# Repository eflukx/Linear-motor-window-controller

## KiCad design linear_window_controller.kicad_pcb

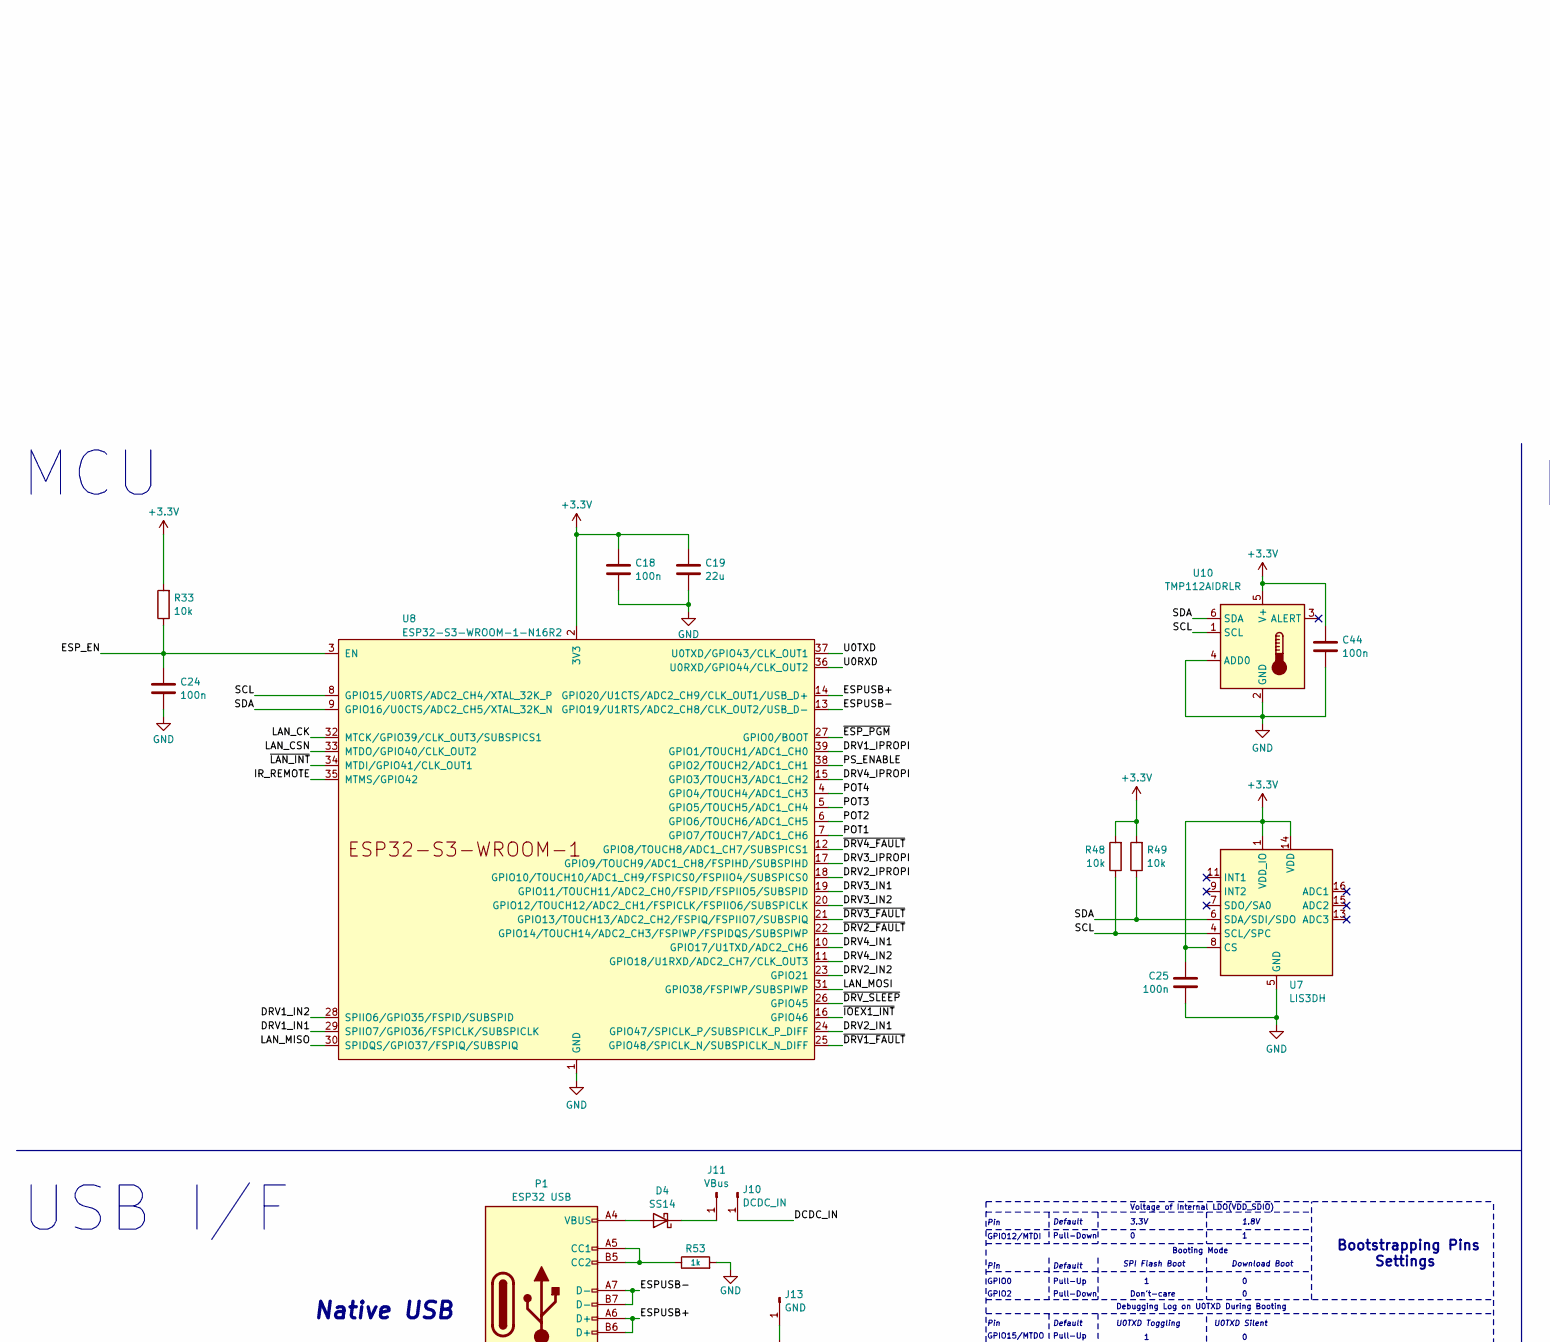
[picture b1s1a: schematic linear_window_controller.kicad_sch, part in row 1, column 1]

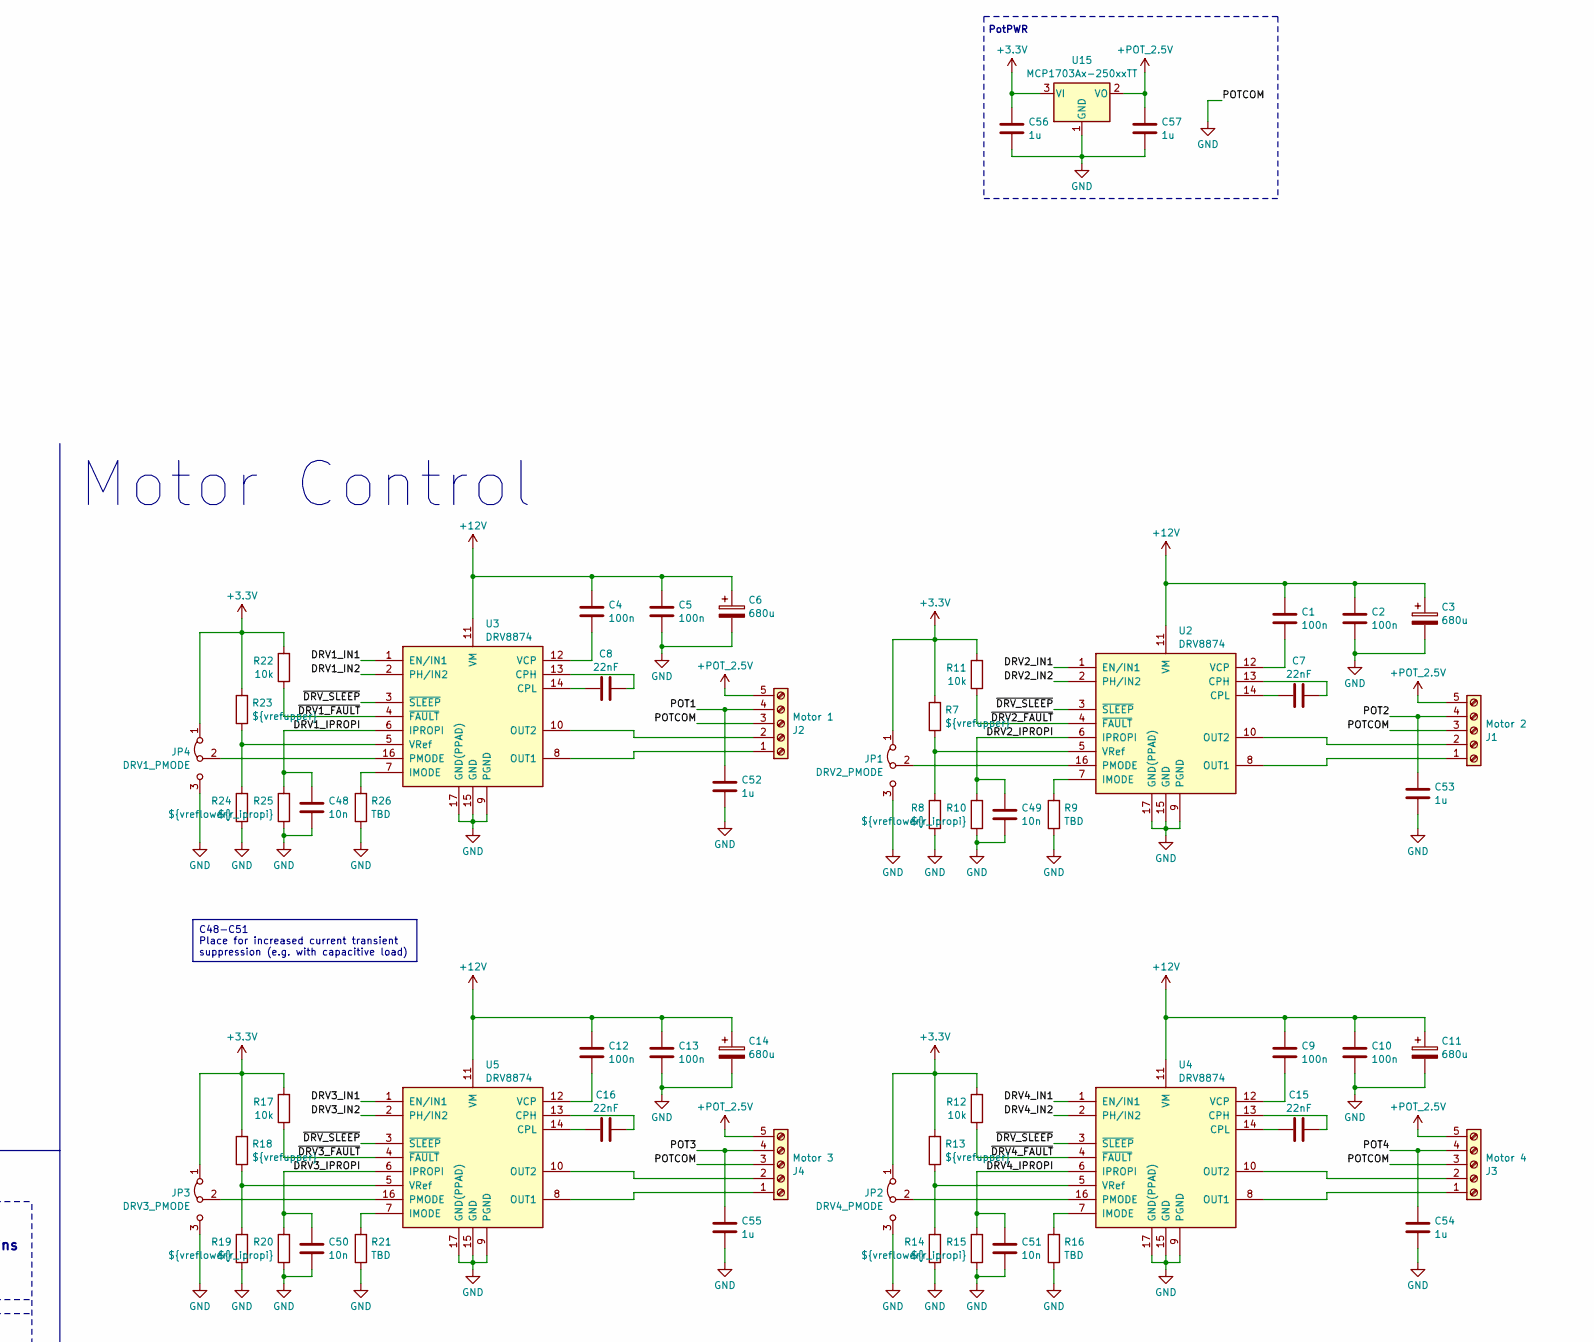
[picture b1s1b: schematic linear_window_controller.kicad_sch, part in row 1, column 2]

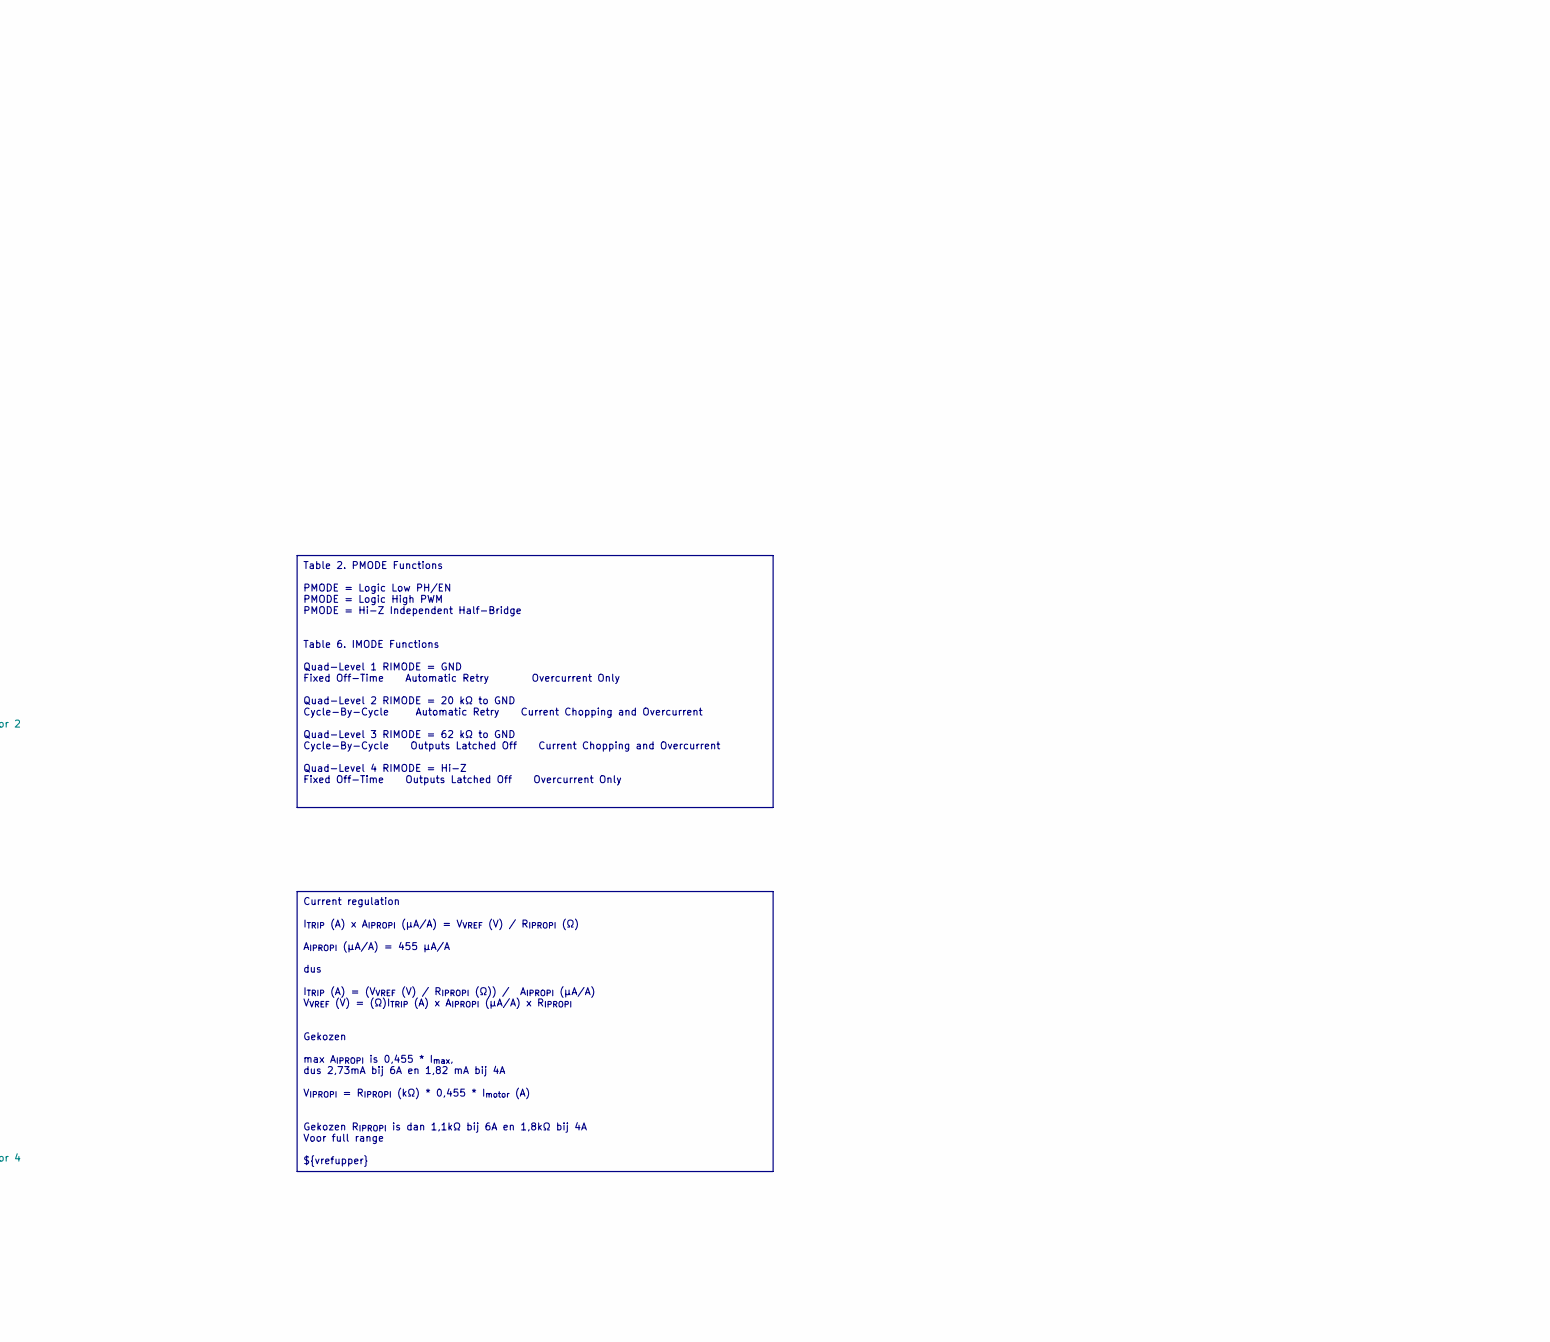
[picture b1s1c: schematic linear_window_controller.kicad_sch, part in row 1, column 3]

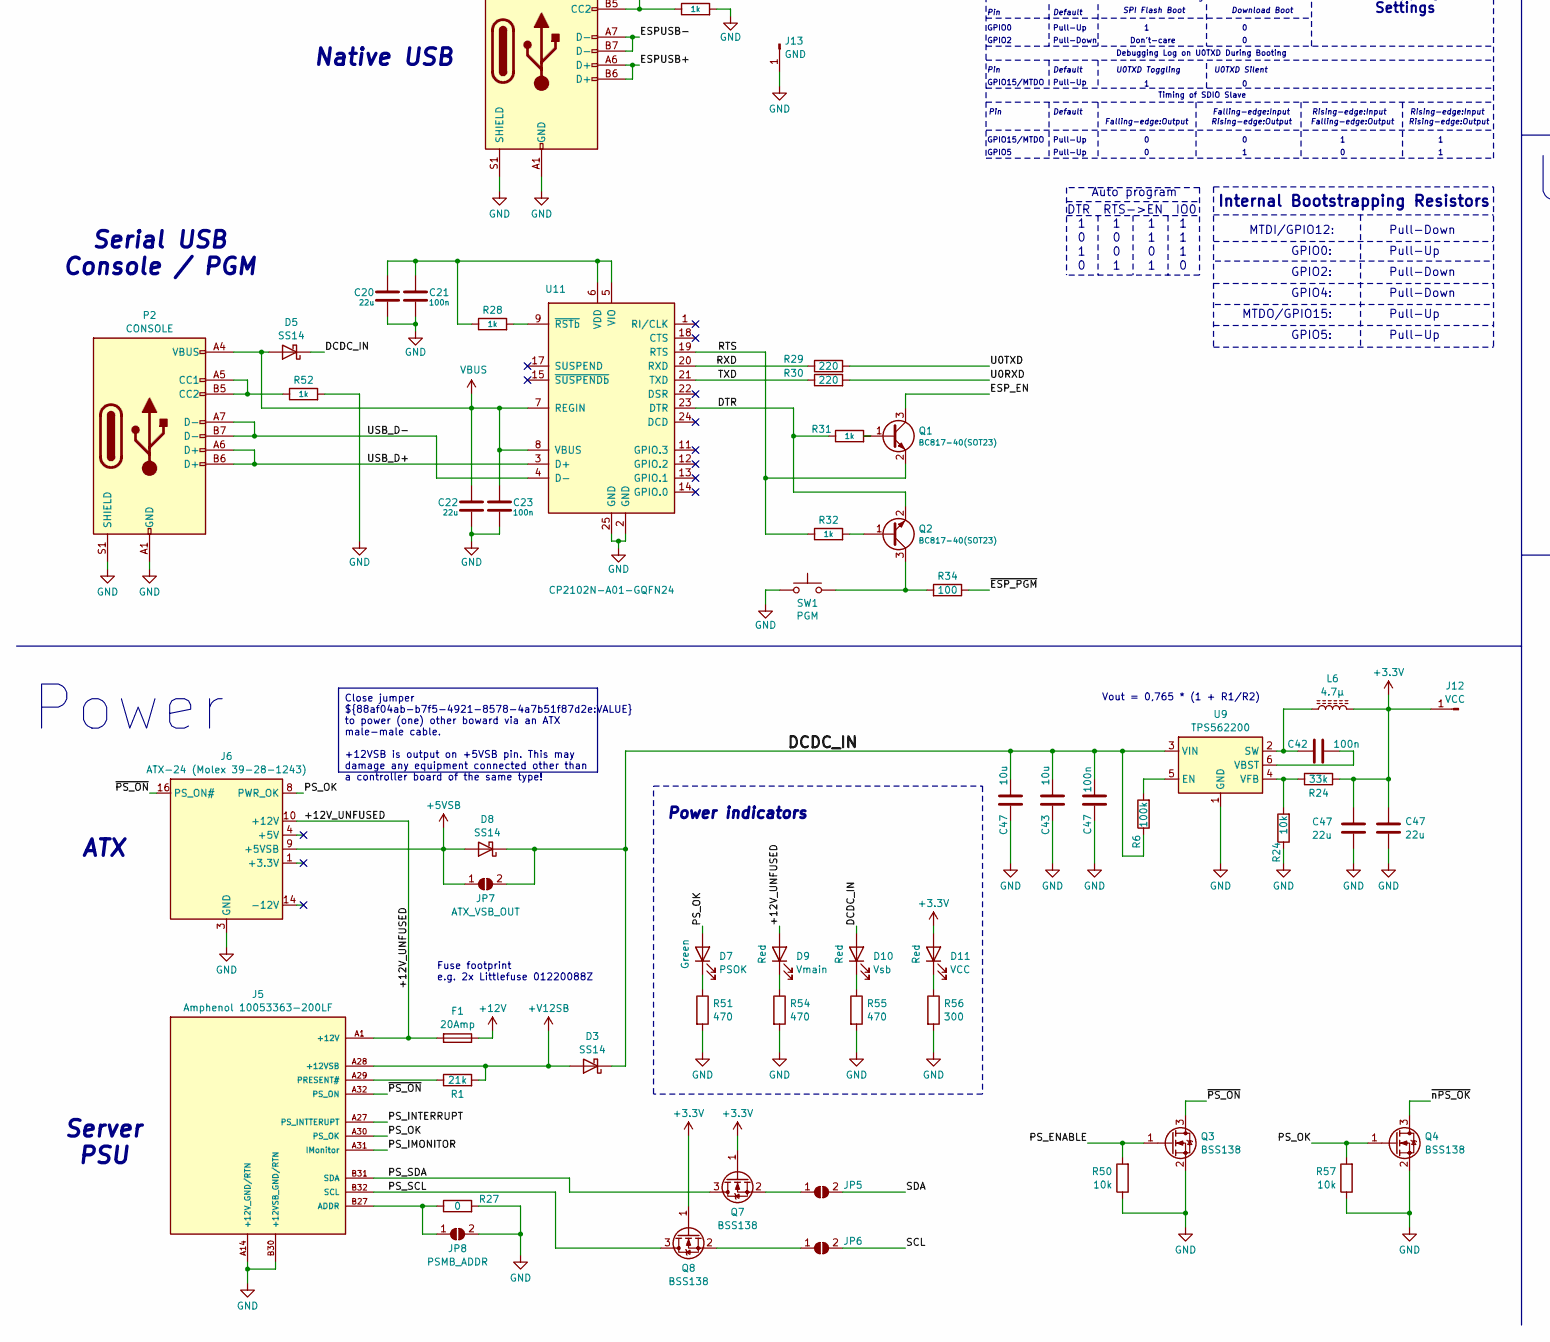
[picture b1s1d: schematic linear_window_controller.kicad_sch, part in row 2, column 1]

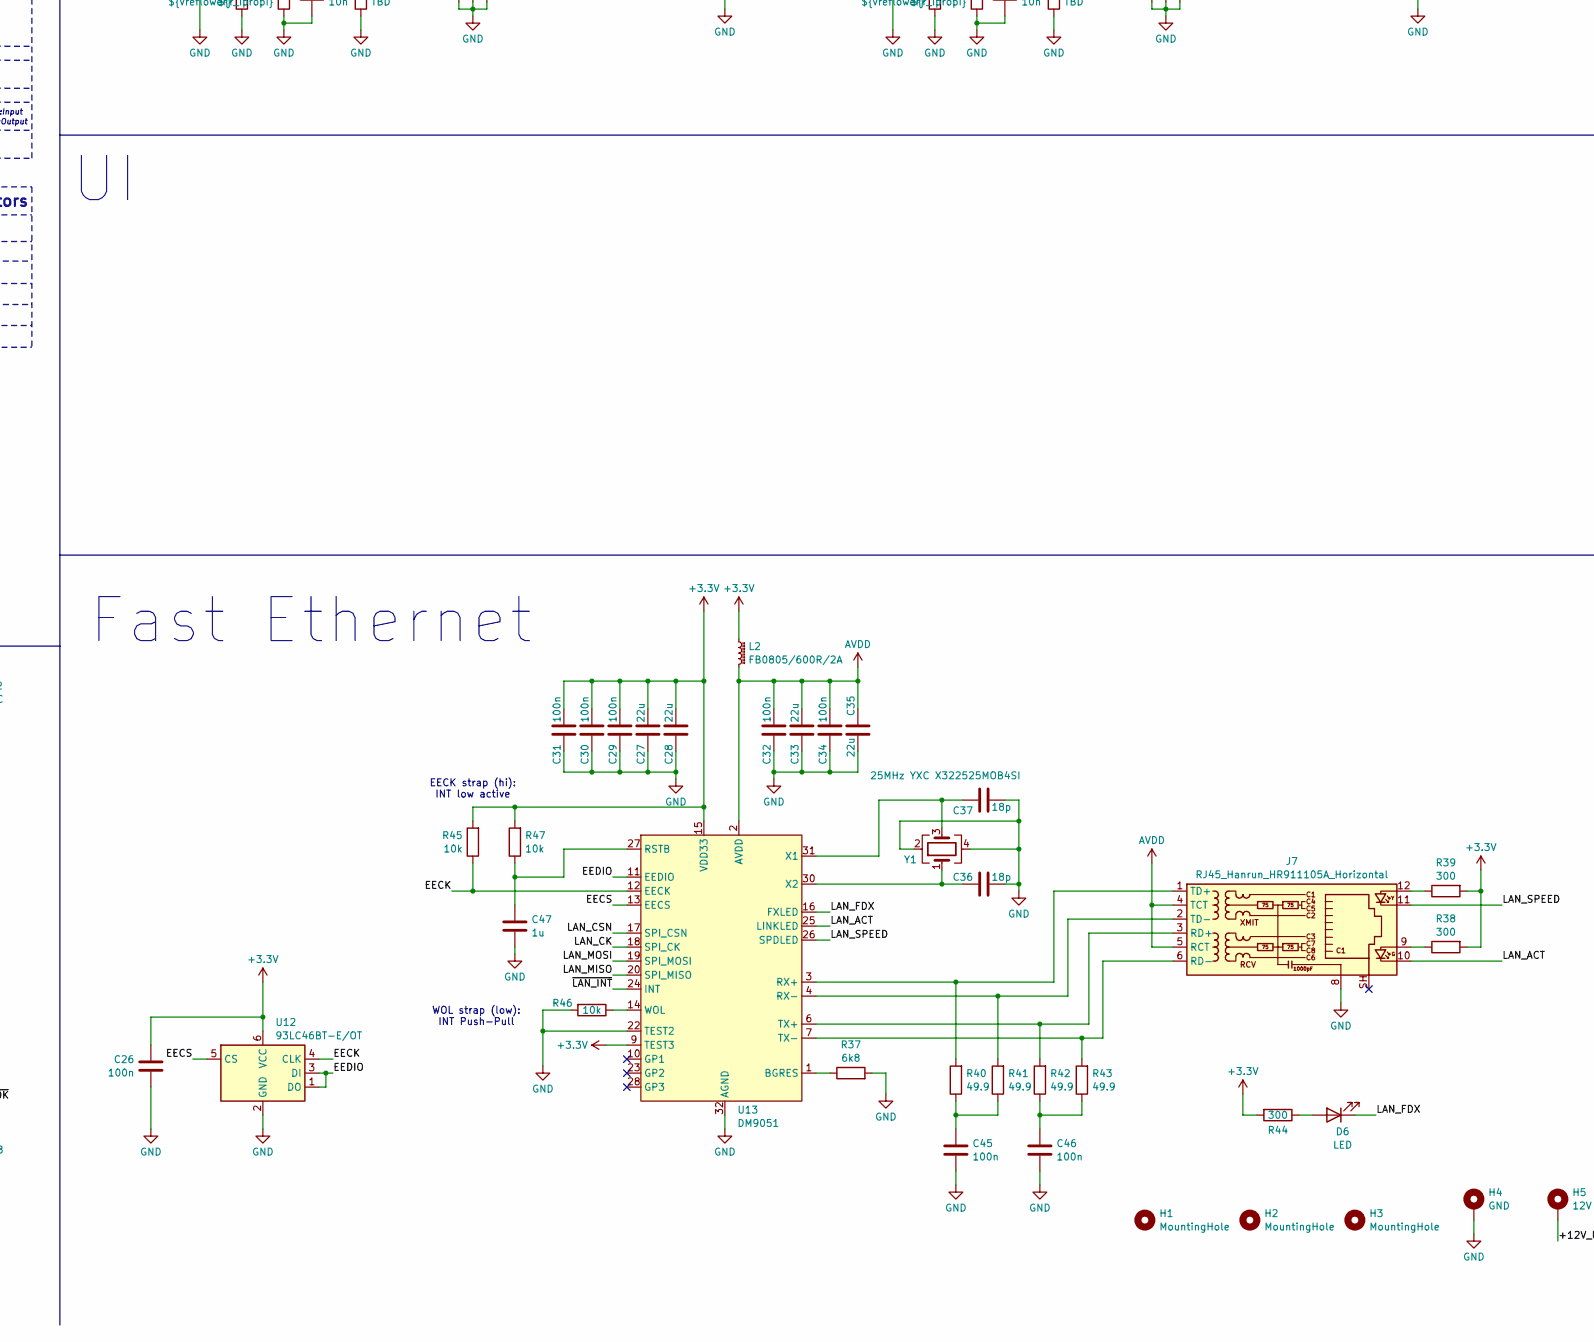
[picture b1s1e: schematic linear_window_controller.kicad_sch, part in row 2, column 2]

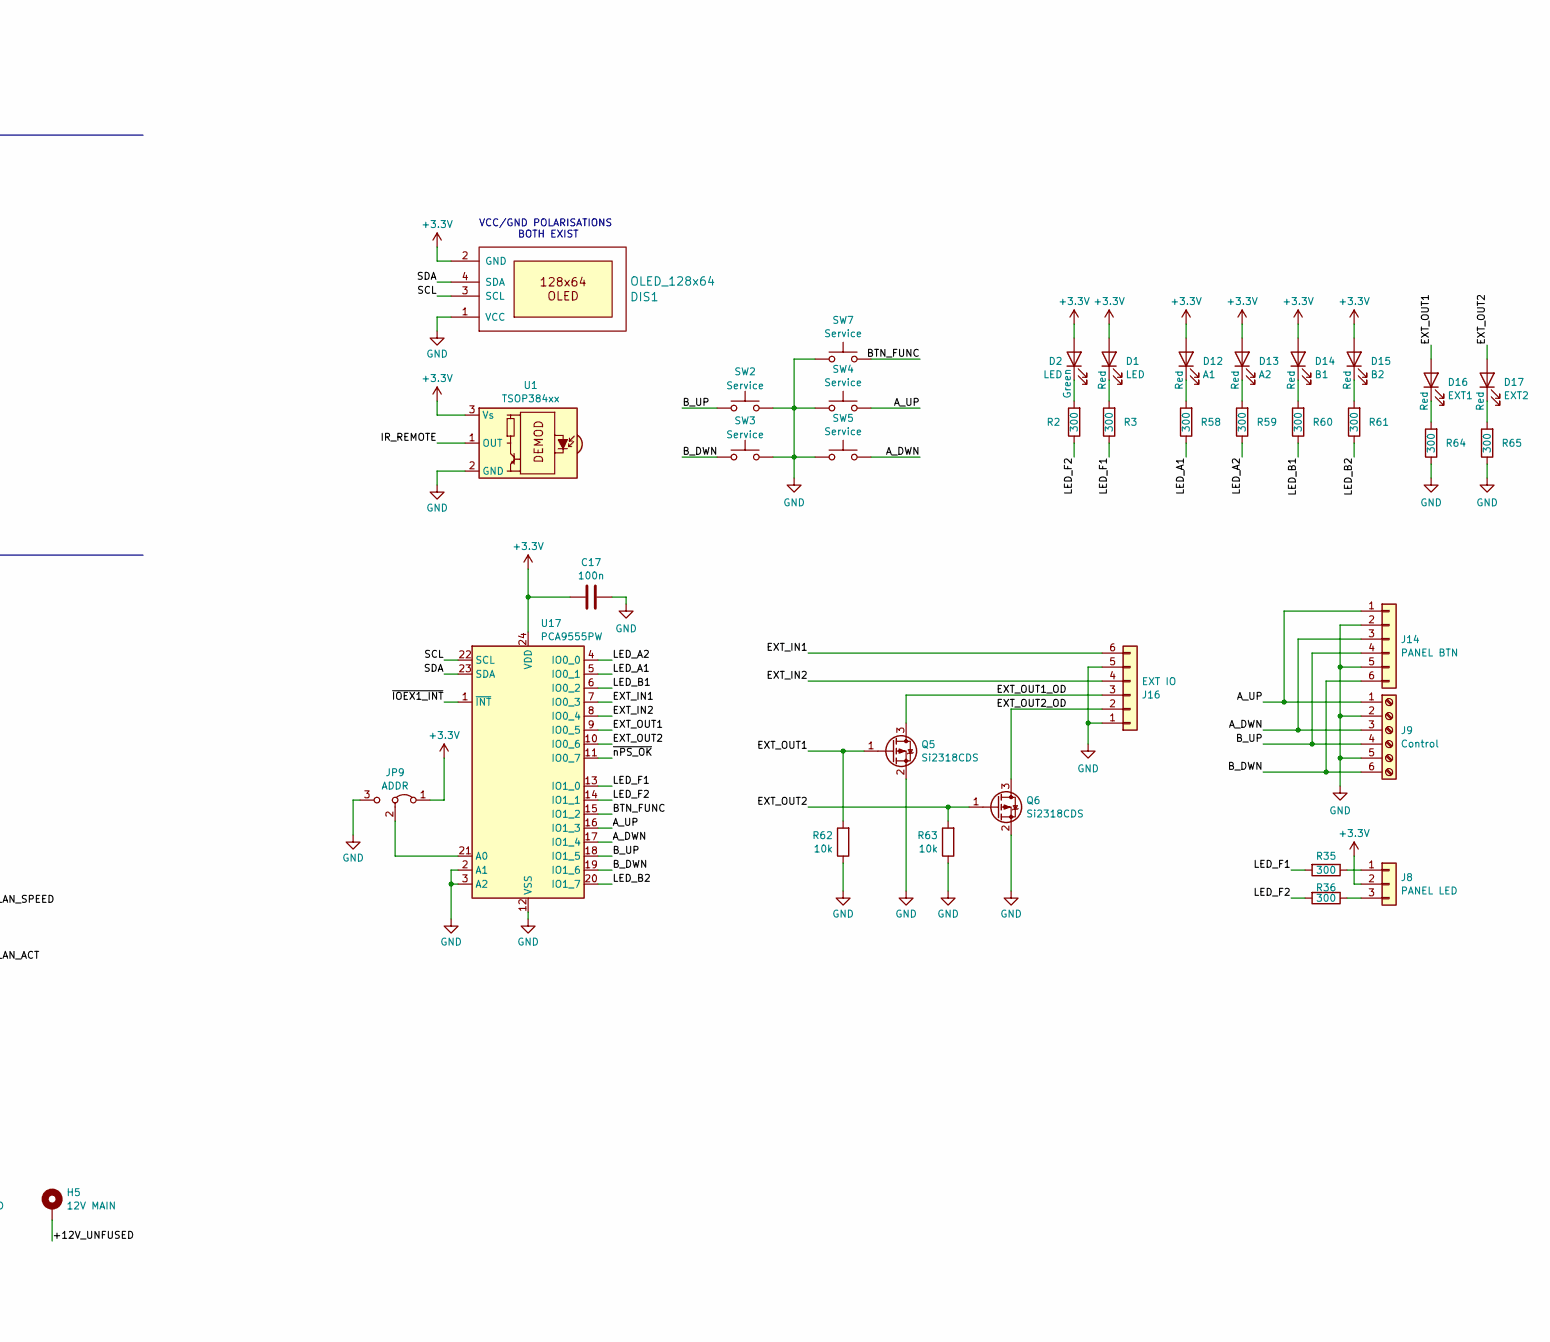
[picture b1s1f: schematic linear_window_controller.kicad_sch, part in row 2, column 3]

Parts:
C1, C2, C4, C5, C9, C10, C12, C13, C17, C18, C21, C23, C24, C25, C26, C29, C30, C31, C32, C34, C42, C44, C45, C46: 100n; C_0603_1608Metric
C3, C6, C11, C14: 680u; CP_Elec_8x10; PartNr 189RV0024; LCSC Part # C7471886
C7, C8, C15, C16: 22nF; C_0603_1608Metric
C19, C20, C22, C27, C28, C33, C35: 22u; C_0603_1608Metric
C36, C37: 18p; C_0603_1608Metric
C43, C47: 10u; C_0603_1608Metric
C48, C49, C50, C51: 10n; C_0603_1608Metric
C52, C53, C54, C55, C56, C57: 1u; C_0603_1608Metric
D1: LED; LED_0603_1608Metric; PartCmnt Red; LCSC Part # C84263
D2, D6: LED; LED_0603_1608Metric; PartCmnt Green; LCSC Part # C7429914
D3, D4, D5, D8: SS14; D_SMA; PartNr SS14; LCSC Part # C2480
D7: PSOK; LED_0603_1608Metric; PartCmnt Green; LCSC Part # C7429914
D9: Vmain; LED_0603_1608Metric; PartCmnt Red; LCSC Part # C84263
D10: Vsb; LED_0603_1608Metric; PartCmnt Red; LCSC Part # C84263
D11: VCC; LED_0603_1608Metric; PartCmnt Red; LCSC Part # C84263
D12: A1; LED_0603_1608Metric; PartCmnt Red; LCSC Part # C84263
D13: A2; LED_0603_1608Metric; PartCmnt Red; LCSC Part # C84263
D14: B1; LED_0603_1608Metric; PartCmnt Red; LCSC Part # C84263
D15: B2; LED_0603_1608Metric; PartCmnt Red; LCSC Part # C84263
D16: EXT1; LED_0603_1608Metric; PartCmnt Red; LCSC Part # C84263
D17: EXT2; LED_0603_1608Metric; PartCmnt Red; LCSC Part # C84263
DIS1: OLED_128x64; OLED_128x64_Module
F1: 20Amp; Fuseholder_Clip-6.3x32mm_Littelfuse_102_122_Inline_P34.21x7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; PartCmnt 2x!; LCSC Part # C206903
H1, H2, H3: MountingHole; MountingHole_3.2mm_M3_Pad_Via
H4: GND; MountingHole_3.2mm_M3_Pad_Via
H5: 12V MAIN; MountingHole_3.2mm_M3_Pad_Via
J1: Motor 2; TerminalBlock_Phoenix_PT-1,5-5-3.5-H_1x05_P3.50mm_Horizontal; PartNr DB125-3.5-5P-GN-S; LCSC Part # C3646874
J2: Motor 1; TerminalBlock_Phoenix_PT-1,5-5-3.5-H_1x05_P3.50mm_Horizontal; PartNr DB125-3.5-5P-GN-S; LCSC Part # C3646874
J3: Motor 4; TerminalBlock_Phoenix_PT-1,5-5-3.5-H_1x05_P3.50mm_Horizontal; PartNr DB125-3.5-5P-GN-S; LCSC Part # C3646874
J4: Motor 3; TerminalBlock_Phoenix_PT-1,5-5-3.5-H_1x05_P3.50mm_Horizontal; PartNr DB125-3.5-5P-GN-S; LCSC Part # C3646874
J5: Amphenol 10053363-200LF; Amphenol_10053363-200LF_WingTAT ER64BGFBK_Compatible_BOTTOM; PartNr ER64BGFBK; LCSC Part # C5173350
J6: ATX-24 (Molex 39-28-1243); Molex_Mini-Fit_Jr_5566-24A_2x12_P4.20mm_Vertical; LCSC Part # C114088
J7: RJ45_Hanrun_HR911105A_Horizontal; PartNr HR913550A or HR911105A; LCSC Part # C163507 or C12074
J8: PANEL LED; PinSocket_1x03_P2.54mm_Vertical
J9: Control; TerminalBlock_Phoenix_PT-1,5-6-3.5-H_1x06_P3.50mm_Horizontal; PartNr 1984659; LCSC Part # C5443903
J10: DCDC_IN; PinHeader_1x01_P2.54mm_Vertical
J11: VBus; PinHeader_1x01_P2.54mm_Vertical
J12: VCC; PinHeader_1x01_P2.54mm_Vertical
J13: GND; TestPoint_Plated_Hole_D2.0mm
J14: PANEL BTN; PinHeader_1x06_P2.54mm_Vertical
J16: EXT IO; PinHeader_1x06_P2.54mm_Vertical
JP1: DRV2_PMODE; SolderJumper-3_P1.3mm_Bridged12_RoundedPad1.0x1.5mm
JP2: DRV4_PMODE; SolderJumper-3_P1.3mm_Bridged12_RoundedPad1.0x1.5mm
JP3: DRV3_PMODE; SolderJumper-3_P1.3mm_Bridged12_RoundedPad1.0x1.5mm
JP4: DRV1_PMODE; SolderJumper-3_P1.3mm_Bridged12_RoundedPad1.0x1.5mm
JP5: PMBUS_DA; SolderJumper-2_P1.3mm_Open_TrianglePad1.0x1.5mm
JP6: PMBUS_CL; SolderJumper-2_P1.3mm_Open_TrianglePad1.0x1.5mm
JP7: ATX_VSB_OUT; SolderJumper-2_P1.3mm_Open_TrianglePad1.0x1.5mm
JP8: PSMB_ADDR; SolderJumper-2_P1.3mm_Open_TrianglePad1.0x1.5mm
JP9: ADDR; SolderJumper-3_P1.3mm_Bridged12_RoundedPad1.0x1.5mm
L2: FB0805/600R/2A; L_0805_2012Metric; PartNr BLM21AG601BH1D; LCSC Part # C524530
L6: 4.7µ; L_Bourns-SRN4018; PartNr SMNR4030-4R7MT; LCSC Part # C135270
P1: ESP32 USB; USB_C_Receptacle_Palconn_UTC16-G; PartNr USB-TYPE-C-019; LCSC Part # C2927039
P2: CONSOLE; USB_C_Receptacle_Palconn_UTC16-G; PartNr USB-TYPE-C-019; LCSC Part # C2927039
Q1, Q2: BC817-40(SOT23); SOT-23; PartNr BC817-40,215; LCSC Part # C52801
Q3, Q4: BSS138; SOT-23; PartNr BSS138-7-F; LCSC Part # C40912
Q5, Q6: Si2318CDS; SOT-23
Q7, Q8: BSS138; SOT-23
R1: 21k; R_0603_1608Metric
R2, R3, R35, R36, R38, R39, R44, R56, R58, R59, R60, R61, R64, R65: 300; R_0603_1608Metric
R6: 100k; R_0603_1608Metric
R7, R13, R18, R23: ${vrefupper}; R_0603_1608Metric
R8, R14, R19, R24: ${vreflower}; R_0603_1608Metric
R9, R16, R21, R26: TBD; R_0603_1608Metric
R10, R15, R20, R25: ${r_ipropi}; R_0603_1608Metric
R11, R12, R17, R22, R33, R45, R46, R47, R48, R49, R50, R57, R62, R63: 10k; R_0603_1608Metric
R27: 0; R_0603_1608Metric
R28, R31, R32, R52, R53: 1k; R_0603_1608Metric
R29, R30: 220; R_0603_1608Metric
R34: 100; R_0603_1608Metric
R37: 6k8; R_0603_1608Metric
R40, R41, R42, R43: 49.9; R_0603_1608Metric
R51, R54, R55: 470; R_0603_1608Metric
SW1: PGM; SW_SPST_B3U-1000P; PartNr B3U-1000P; LCSC Part # C231329
SW2, SW3, SW4, SW5, SW7: Service; SW_SPST_TL3305B; PartNr TSC015A04818B; LCSC Part # C2888508
U1: TSOP384xx; Vishay_MINICAST-3Pin
U2, U3, U4, U5: DRV8874; HTSSOP-16-1EP_4.4x5mm_P0.65mm_EP3.4x5mm_Mask3x3mm_ThermalVi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; PartNr DRV8874PWPR; LCSC Part # C1855818
U7: LIS3DH; LGA-16_3x3mm_P0.5mm_LayoutBorder3x5y
U8: ESP32-S3-WROOM-1-N16R2; ESP32-S3-WROOM-1; PartNr ESP32-S3-WROOM-1-N16R2; LCSC Part # C2913205
U9: TPS562200; SOT-23-6; PartNr TPS562200DDCR; LCSC Part # C49757
U10: TMP112AIDRLR; SOT-563; PartNr TMP112AIDRLR; LCSC Part # C28927
U11: CP2102N-A01-GQFN24; QFN-24-1EP_4x4mm_P0.5mm_EP2.6x2.6mm; PartNr CP2102N-A02-GQFN24R; LCSC Part # C969151
U12: 93LC46BT-E/OT; SOT-23-6; PartNr 93LC46BT-E/OT; LCSC Part # C2061604
U13: DM9051; QFN-32-1EP_5x5mm_P0.5mm_EP3.3x3.3mm_ThermalVias; PartNr DM9051NP; LCSC Part # C113756
U15: MCP1703Ax-250xxTT; SOT-23
U17: PCA9555PW; TSSOP-24_4.4x7.8mm_P0.65mm
Y1: 25MHz YXC X322525MOB4SI; Crystal_SMD_3225-4Pin_3.2x2.5mm; PartNr X322525MOB4SI; LCSC Part # C9006

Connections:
+5VSB: D8.2 (A), J6.9 (+5VSB), JP7.1 (A)
+12V: C1.1, C2.2, C3.1, C4.1, C5.2, C6.1, C9.1, C10.2, C11.1, C12.1, C13.2, C14.1, F1.1, U2.11 (VM), U3.11 (VM), U4.11 (VM), U5.11 (VM)
+POT_2.5V: C57.1, J1.5, J2.5, J3.5, J4.5, U15.2 (VO)
+V12SB: D3.2 (A), J5.A28 (+12VSB), R1.2
/+12V_UNFUSED: D9.2 (A), F1.2, H5.1, J5.A1 (+12V), J5.A2 (+12V), J5.A3 (+12V), J5.A4 (+12V), J5.A5 (+12V), J5.A6 (+12V), J5.A7 (+12V), J5.A8 (+12V), J5.A9 (+12V), J5.A10 (+12V), J5.A11 (+12V), J5.A12 (+12V), J5.A13 (+12V), J5.B1 (+12V), J5.B2 (+12V), J5.B3 (+12V), J5.B4 (+12V), J5.B5 (+12V), J5.B6 (+12V), J5.B7 (+12V), J5.B8 (+12V), J5.B9 (+12V), J5.B10 (+12V), J5.B11 (+12V), J5.B12 (+12V), J5.B13 (+12V), J6.10 (+12V), J6.11 (+12V)
/A_DWN: J9.3, J14.3, SW5.2, U17.17 (IO1_4)
/A_UP: J9.1, J14.1, SW4.2, U17.16 (IO1_3)
/BTN_FUNC: SW7.2, U17.15 (IO1_2)
/B_DWN: J9.6, J14.6, SW3.2, U17.19 (IO1_6)
/B_UP: J9.4, J14.4, SW2.2, U17.18 (IO1_5)
/DRV1_IN1: U3.1 (EN/IN1), U8.29 (SPIIO7/GPIO36/FSPICLK/SUBSPICLK)
/DRV1_IN2: U3.2 (PH/IN2), U8.28 (SPIIO6/GPIO35/FSPID/SUBSPID)
/DRV1_IPROPI: C48.1, R25.2, U3.6 (IPROPI), U8.39 (GPIO1/TOUCH1/ADC1_CH0)
/DRV2_IN1: U2.1 (EN/IN1), U8.24 (GPIO47/SPICLK_P/SUBSPICLK_P_DIFF)
/DRV2_IN2: U2.2 (PH/IN2), U8.23 (GPIO21)
/DRV2_IPROPI: C49.1, R10.2, U2.6 (IPROPI), U8.18 (GPIO10/TOUCH10/ADC1_CH9/FSPICS0/FSPIIO4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)
/DRV3_IN1: U5.1 (EN/IN1), U8.19 (GPIO11/TOUCH11/ADC2_CH0/FSPID/FSPIIO5/S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)
/DRV3_IN2: U5.2 (PH/IN2), U8.20 (GPIO12/TOUCH12/ADC2_CH1/FSPICLK/FSPIIO6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)
/DRV3_IPROPI: C50.1, R20.2, U5.6 (IPROPI), U8.17 (GPIO9/TOUCH9/ADC1_CH8/FSPIHD/SUBSPIHD)
/DRV4_IN1: U4.1 (EN/IN1), U8.10 (GPIO17/U1TXD/ADC2_CH6)
/DRV4_IN2: U4.2 (PH/IN2), U8.11 (GPIO18/U1RXD/ADC2_CH7/CLK_OUT3)
/DRV4_IPROPI: C51.1, R15.2, U4.6 (IPROPI), U8.15 (GPIO3/TOUCH3/ADC1_CH2)
/DTR: Q2.2 (E), R31.1, U11.23 (DTR)
/EECK: R45.1, U12.4 (CLK), U13.12 (EECK)
/EECS: U12.5 (CS), U13.13 (EECS)
/EEDIO: U12.1 (DO), U12.3 (DI), U13.11 (EEDIO)
/ESPUSB+: P1.A6 (D+), P1.B6 (D+), U8.14 (GPIO20/U1CTS/ADC2_CH9/CLK_OUT1/USB_D+)
/ESPUSB-: P1.A7 (D-), P1.B7 (D-), U8.13 (GPIO19/U1RTS/ADC2_CH8/CLK_OUT2/USB_D-)
/ESP_EN: C24.1, Q1.3 (C), R33.1, U8.3 (EN)
/EXT_IN1: J16.6, U17.7 (IO0_3)
/EXT_IN2: J16.4, U17.8 (IO0_4)
/EXT_OUT1: D16.2 (A), Q5.1 (G), R62.2, U17.9 (IO0_5)
/EXT_OUT1_OD: J16.3, Q5.3 (D)
/EXT_OUT2: D17.2 (A), Q6.1 (G), R63.2, U17.10 (IO0_6)
/EXT_OUT2_OD: J16.2, Q6.3 (D)
/IR_REMOTE: U1.1 (OUT), U8.35 (MTMS/GPIO42)
/LAN_ACT: J7.10, U13.25 (LINKLED)
/LAN_CK: U8.32 (MTCK/GPIO39/CLK_OUT3/SUBSPICS1), U13.18 (SPI_CK)
/LAN_CSN: U8.33 (MTDO/GPIO40/CLK_OUT2), U13.17 (SPI_CSN)
/LAN_FDX: D6.1 (K), U13.16 (FXLED)
/LAN_MISO: U8.30 (SPIDQS/GPIO37/FSPIQ/SUBSPIQ), U13.20 (SPI_MISO)
/LAN_MOSI: U8.31 (GPIO38/FSPIWP/SUBSPIWP), U13.19 (SPI_MOSI)
/LAN_SPEED: J7.11, U13.26 (SPDLED)
/LED_A1: R58.1, U17.5 (IO0_1)
/LED_A2: R59.1, U17.4 (IO0_0)
/LED_B1: R60.1, U17.6 (IO0_2)
/LED_B2: R61.1, U17.20 (IO1_7)
/LED_F1: R3.1, R35.2, U17.13 (IO1_0)
/LED_F2: R2.1, R36.2, U17.14 (IO1_1)
/POT1: C52.1, J2.4, U8.7 (GPIO7/TOUCH7/ADC1_CH6)
/POT2: C53.1, J1.4, U8.6 (GPIO6/TOUCH6/ADC1_CH5)
/POT3: C55.1, J4.4, U8.5 (GPIO5/TOUCH5/ADC1_CH4)
/POT4: C54.1, J3.4, U8.4 (GPIO4/TOUCH4/ADC1_CH3)
/PS_ENABLE: Q3.1 (G), R50.2, U8.38 (GPIO2/TOUCH2/ADC1_CH1)
/PS_IMONITOR: J5.A31 (IMonitor)
/PS_INTERRUPT: J5.A27 (PS_INTTERUPT)
/PS_OK: D7.2 (A), J5.A30 (PS_OK), J6.8 (PWR_OK), Q4.1 (G), R57.2
/PS_SCL: J5.B32 (SCL), Q8.3 (D)
/PS_SDA: J5.B31 (SDA), Q7.3 (D)
/RTS: Q1.2 (E), R32.1, U11.19 (RTS)
/RXD: R29.1, U11.20 (RXD)
/SCL: DIS1.3 (SCL), JP6.2 (B), R48.1, U7.4 (SCL/SPC), U8.8 (GPIO15/U0RTS/ADC2_CH4/XTAL_32K_P), U10.1 (SCL), U17.22 (SCL)
/SDA: DIS1.4 (SDA), JP5.2 (B), R49.1, U7.6 (SDA/SDI/SDO), U8.9 (GPIO16/U0CTS/ADC2_CH5/XTAL_32K_N), U10.6 (SDA), U17.23 (SDA)
/TXD: R30.1, U11.21 (TXD)
/U0RXD: R30.2, U8.36 (U0RXD/GPIO44/CLK_OUT2)
/U0TXD: R29.2, U8.37 (U0TXD/GPIO43/CLK_OUT1)
/USB_D+: P2.A6 (D+), P2.B6 (D+), U11.3 (D+)
/USB_D-: P2.A7 (D-), P2.B7 (D-), U11.4 (D-)
/~DRV1_FAULT: R22.1, U3.4 (~FAULT), U8.25 (GPIO48/SPICLK_N/SUBSPICLK_N_DIFF)
/~DRV2_FAULT: R11.1, U2.4 (~FAULT), U8.22 (GPIO14/TOUCH14/ADC2_CH3/FSPIWP/FSPIDQS/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)
/~DRV3_FAULT: R17.1, U5.4 (~FAULT), U8.21 (GPIO13/TOUCH13/ADC2_CH2/FSPIQ/FSPIIO7/S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)
/~DRV4_FAULT: R12.1, U4.4 (~FAULT), U8.12 (GPIO8/TOUCH8/ADC1_CH7/SUBSPICS1)
/~DRV_SLEEP: U2.3 (~SLEEP), U3.3 (~SLEEP), U4.3 (~SLEEP), U5.3 (~SLEEP), U8.26 (GPIO45)
/~ESP_PGM: R34.1, U8.27 (GPIO0/BOOT)
/~IOEX1_INT: U8.16 (GPIO46), U17.1 (~INT)
/~LAN_INT: U8.34 (MTDI/GPIO41/CLK_OUT1), U13.24 (INT)
/~PS_ON: J5.A32 (PS_ON), J6.16 (PS_ON#), Q3.3 (D)
/~nPS_OK: Q4.3 (D), U17.11 (IO0_7)
AVDD: C32.2, C33.2, C34.2, C35.1, J7.4 (TCT), J7.5 (RCT), L2.2, U13.2 (AVDD), U13.8 (AVDD)
unnamed: C45.1, R40.1, R41.1
unnamed: C46.1, R42.1, R43.1
unnamed: D1.1 (K), R3.2
unnamed: D2.1 (K), R2.2
unnamed: D4.2 (A), P1.A4 (VBUS), P1.A9 (VBUS), P1.B4 (VBUS), P1.B9 (VBUS)
unnamed: D4.1 (K), J11.1
unnamed: D6.2 (A), R44.1
unnamed: D7.1 (K), R51.1
unnamed: D9.1 (K), R54.1
unnamed: D10.1 (K), R55.1
unnamed: D11.1 (K), R56.1
unnamed: D12.1 (K), R58.2
unnamed: D13.1 (K), R59.2
unnamed: D14.1 (K), R60.2
unnamed: D15.1 (K), R61.2
unnamed: D16.1 (K), R64.2
unnamed: D17.1 (K), R65.2
unnamed: J1.1, U2.8 (OUT1)
unnamed: J1.2, U2.10 (OUT2)
unnamed: J2.1, U3.8 (OUT1)
unnamed: J2.2, U3.10 (OUT2)
unnamed: J3.1, U4.8 (OUT1)
unnamed: J3.2, U4.10 (OUT2)
unnamed: J4.1, U5.8 (OUT1)
unnamed: J4.2, U5.10 (OUT2)
unnamed: J5.B27 (ADDR), JP8.1 (A), R27.1
unnamed: J5.A29 (PRESENT#), R1.1
unnamed: J7.9, R38.1
unnamed: J7.12, R39.1
unnamed: J7.3 (RD+), R42.2, U13.6 (TX+)
unnamed: J7.6 (RD-), R43.2, U13.7 (TX-)
unnamed: J7.1 (TD+), R40.2, U13.3 (RX+)
unnamed: J7.2 (TD-), R41.2, U13.4 (RX-)
unnamed: J8.1, R35.1
unnamed: J8.3, R36.1
unnamed: JP1.2 (C), U2.16 (PMODE)
unnamed: JP2.2 (C), U4.16 (PMODE)
unnamed: JP3.2 (C), U5.16 (PMODE)
unnamed: JP4.2 (C), U3.16 (PMODE)
unnamed: JP5.1 (A), Q7.2 (S)
unnamed: JP6.1 (A), Q8.2 (S)
unnamed: JP9.2 (C), U17.21 (A0)
unnamed: P1.A5 (CC1), P1.B5 (CC2), R53.1
unnamed: P2.A5 (CC1), P2.B5 (CC2), R52.1
unnamed: Q1.1 (B), R31.2
unnamed: Q2.1 (B), R32.2
unnamed: Q2.3 (C), R34.2, SW1.2
unnamed: C7.2, U2.13 (CPH)
unnamed: C7.1, U2.14 (CPL)
unnamed: R9.2, U2.7 (IMODE)
unnamed: C1.2, U2.12 (VCP)
unnamed: R7.1, R8.2, U2.5 (VRef)
unnamed: C8.2, U3.13 (CPH)
unnamed: C8.1, U3.14 (CPL)
unnamed: R26.2, U3.7 (IMODE)
unnamed: C4.2, U3.12 (VCP)
unnamed: C15.2, U4.13 (CPH)
unnamed: C15.1, U4.14 (CPL)
unnamed: R16.2, U4.7 (IMODE)
unnamed: C9.2, U4.12 (VCP)
unnamed: R13.1, R14.2, U4.5 (VRef)
unnamed: C16.2, U5.13 (CPH)
unnamed: C16.1, U5.14 (CPL)
unnamed: R21.2, U5.7 (IMODE)
unnamed: C12.2, U5.12 (VCP)
unnamed: R18.1, R19.2, U5.5 (VRef)
unnamed: R6.2, U9.5 (EN)
unnamed: C42.2, L6.1, U9.2 (SW)
unnamed: C42.1, U9.6 (VBST)
unnamed: C20.1, C21.1, R28.1, U11.5 (VIO), U11.6 (VDD)
unnamed: R28.2, U11.9 (~RSTb)
unnamed: R37.1, U13.1 (BGRES)
unnamed: R46.1, U13.14 (WOL)
unnamed: C37.2, U13.31 (X1), Y1.3
unnamed: C36.2, U13.30 (X2), Y1.1
VBUS: C22.1, C23.1, D5.2 (A), P2.A4 (VBUS), P2.A9 (VBUS), P2.B4 (VBUS), P2.B9 (VBUS), U11.7 (REGIN), U11.8 (VBUS)

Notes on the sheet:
Current regulation I_{TRIP} (A) x A_{IPROPI} (μA/A) = V_{VREF} (V) / R_{IPROPI} (Ω) A_{IPROPI} (μA/A) = 455 µA/A dus I_{TRIP} (A) = (V_{VREF} (V) / R_{IPROPI} (Ω)) / A_{IPROPI} (μA/A) V_{VREF} (V) = (Ω)I_{TRIP} (A) x A_{IPROPI} (μA/A) x R_{IPROPI} Gekozen max A_{IPROPI} is 0,455 * I_{max}, dus 2,73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
Close jumper ${88af04ab-b7f5-4921-8578-4a7b51f87d2e:VALUE} to power (one) other boward via an ATX male-male cable. +12VSB is output on +5VSB pin. This may damage any equipment connected other than a controller board of the same type!
Table 2. PMODE Functions PMODE = Logic Low PH/EN PMODE = Logic High PWM PMODE = Hi-Z Independent Half-Bridge Table 6. IMODE Functions Quad-Level 1 RIMODE = GND Fixed Off-Time Automatic Retry Overcurrent Only Quad-Level 2 RIMODE = 20 kΩ to GND Cycle-By-Cycle Automatic Retry Current Chopping and Over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
C48-C51 Place for increased current transient suppression (e.g. with capacitive load)
Rising-edge:Output
Voltage of Internal LDO(VDD_SDIO)
Motor Control
MTDO/GPIO15:
Pull-Up
GPIO2:
3.3V
Pull-Down
Power indicators
Pin
Booting Mode
Internal Bootstrapping Resistors
Falling-edge:Input
Vout = 0,765 * (1 + R1/R2)
Rising-edge:Input
Don't-care
MTDI/GPIO12:
Falling-edge:Output
GPIO5
GPIO5:
Default
GPIO12/MTDI
U0TXD Toggling
Server PSU
VCC/GND POLARISATIONS BOTH EXIST
WOL strap (low): INT Push-Pull
1.8V
GPIO0:
U0TXD Silent
SPI Flash Boot
PotPWR
Auto program
GPIO2
Timing of SDIO Slave
GPIO15/MTDO
Bootstrapping Pins Settings

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

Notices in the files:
linear_window_controller.kicad_pcb:
(c) 2024 iotta
